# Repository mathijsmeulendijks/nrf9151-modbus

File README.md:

# nRF9151 multi-protocol industrial node

DIN-rail board (3D-printed 2-module housing, TS35): **85-264 VAC** (Mean Well IRM-10-5) -> **discrete CC supercap charger** hold-up (0.1 ohm + INA180A1 + MCP6001 + AO4407A) -> **nRF9151** cellular/GNSS with **RS-485 + RS-232 + CAN** on one RJ45.

Native **KiCad 10** project. Schematic is the source of truth for circuits; the PCB is fully placed but **unrouted** (routing is done by the board designer). The PCB stands vertical in a DIN 43880 housing (2 modules, 36 mm wide).

## Architecture

| Block | Implementation |
|-------|----------------|
| Mains in | Phoenix MKDS 1,5 2-pos 5.08 mm terminal J1 (no LCSC number yet) |
| Mains fuse | **SMD 2410 fuse** JFC2410-1100TS (1 A time-lag, 250 V, C136380) -> IRM-10-5 (C2857903) |
| Supercap charge | **Discrete CC**: 0.1 ohm sense + **INA180A1** + **MCP6001** + **AO4407A** P-FET (~0.5 A) |
| Hold-up | **3.5 F / 5.5 V** CDA CHP5R5L355R-TW (C2925904, 20x10x22 mm upright) + **dual LM66100** ideal-diode OR into VSYS |
| Surge | **SMAJ5.0A** on VSYS |
| Brownout | APX803L-29 (2.9 V UVLO -> nRESET) + VSYS ADC on P0.04 |
| 3.3 V | TLV1117-33 (peripherals + **VDD_GPIO**) |
| Modem VDD | **VSYS (~4-5 V)** through FB + bulk (not 3.3 V) |
| MCU/modem | NRF9151-LACA-R |
| RF | LTE + GNSS IPEX + **PESD5V0F1BL** RF ESD; AUX 49.9 ohm |
| SIM | Push-push nano-SIM (C7529384), **22 ohm** series, **USBLC6-2** + PESD ESD; physical SIM plus optional Onomondo SoftSIM in firmware (no eSIM lock-in) |
| RS-485 | **TI ISOW1412** isolated transceiver + iso DC-DC; **SM712** TVS |
| RS-232 | **TI MAX3232IPWR**; 2x **SMBJ15CA** TVS |
| CAN | MCP2515-I/ST TSSOP-20 (SPI, C15193) + **TI SN65HVD230** + 8 MHz crystal (C2682774); **NUP2105LT1G** on CAN H/L |
| Field I/O | Single RJ45 (KH-RJ45-56-8P8C) |
| Debug | 10-pin SWD; SWDIO 10 k up, **SWDCLK 100 k down**; no reset switch (reset via UVLO, SWD, nRESET test pad) |
| Temp | TMP117 on I2C |

## Power path

```
AC_L -> SMD fuse -> IRM-10-5 -> 5V_RAW
                         |- Rsense + P-FET CC -> supercap -+
                         '- LM66100 -----------------------+-> VSYS -+-> LDO 3V3 -> VDD_GPIO / logic
                                                           |         '-> FB -> VDD_nRF (SiP VDD)
                         supercap -> LM66100 --------------+
VSYS <- SMAJ5.0A clamp
```

**Why VDD from VSYS:** Nordic VDD is 3.0-5.5 V; RF headroom and TX efficiency are better above 3.3 V. VDD_GPIO stays at 3.3 V for ISOW / MAX3232 / CAN / SWD levels.

**Ideal diodes:** LM66100 (~95 mohm) replace a Schottky OR so hold-up loses less voltage under load.

## Supercap charge limiter (FET + op-amp)

| Piece | Role |
|-------|------|
| **0.1 ohm** 1206 sense | V_sense = I * R (50 mV @ 0.5 A) |
| **INA180A1** (20 V/V) | High-side sense -> V_fb ~ 1.0 V @ 0.5 A |
| Divider 40.2k/10k | V_ref ~ 1.0 V from 5 V |
| **MCP6001** | Error amp: V_fb > V_ref raises P-FET gate (less current) |
| **AO4407A** SOP-8 | P-FET handles linear heat; ~fully on when I < I_set for top-up |

```
I_set ~ V_ref / (G_INA * R_sense) ~ 1.0 / (20 * 0.1) = 0.5 A
```

Pour copper under AO4407A; keep sense Kelvin-ish. SMAJ5.0A clamps VSYS (not a precision CV for the 5.5 V cap, which charges to ~5V_RAW).

## Field RJ45 pinout (custom multi-bus)

| Pin | Signal |
|-----|--------|
| 1-2 | RS485_A / B (isolated; **not** board GND) |
| 3 / 6 | RS232_TX / RX |
| 4-5 | CAN_H / L |
| 7-8 | GND (RS-232 / CAN reference) |
| 9-10 | Shield -> board GND |

## MCU pin map

| Function | Pins |
|----------|------|
| RS-485 UART | P0.10 TX, P0.11 RX, P0.12 DE (/RE) |
| RS-232 UART | P0.13 TX, P0.14 RX |
| CAN SPI | P0.15 SCK, P0.16 MOSI, P0.17 MISO, P0.18 nCS, P0.19 nINT |
| I2C temp | P0.02 SDA, P0.03 SCL |
| VSYS ADC | P0.04 |

## Project files

| File | Content |
|------|---------|
| `nrf9151-modbus.kicad_pro` / `.kicad_sch` | Project and root sheet |
| `power.kicad_sch` | Mains, charger, hold-up, VSYS, 3V3, UVLO |
| `nrf9151.kicad_sch` | SiP, decoupling, RF, SIM, SWD, temp |
| `rs485.kicad_sch` | Isolated RS-485 |
| `fieldbus.kicad_sch` | Fieldbus RS-232, CAN, RJ45 |
| `nrf9151-modbus.kicad_pcb` | 4-layer, 86 x 56 mm DIN outline (body 86 x 44 + nose 41 x 12), all 144 parts on top, 49 bare test pads on the bottom, unrouted |
| `nrf9151-modbus.kicad_dru` | Custom DRC rules (JLC minimums, mains and isolation clearances) |
| `lib/jlc.kicad_sym`, `lib/jlc.pretty`, `lib/jlc.3dshapes` | Project-local LCSC part library (3D models via Git LFS) |

Board is single-sided assembly: the bottom carries only test pads for the bed-of-nails tester (incl. a 5-pad SWD row), no mains nets. See `HANDOFF.md` for decisions, SIM strategy, open items and bring-up checklist.

## Open and fabricate

1. Open `nrf9151-modbus.kicad_pro` in **KiCad 10**.
2. Run ERC and DRC (`kicad-cli pcb drc --schematic-parity`) before fab.
3. BOM/CPL: install **Bouni/kicad-jlcpcb-tools** via the Plugin and Content Manager (reads the `LCSC` field; check rotations in the JLC preview), or **bennymeg Fabrication-Toolkit >= 5.3.1**.
4. Order with JLCPCB stackup **JLC04161H-7628** (1.6 mm, 4 layer); use the JLC impedance calculator for the 50 ohm ANT/GPS microstrips.

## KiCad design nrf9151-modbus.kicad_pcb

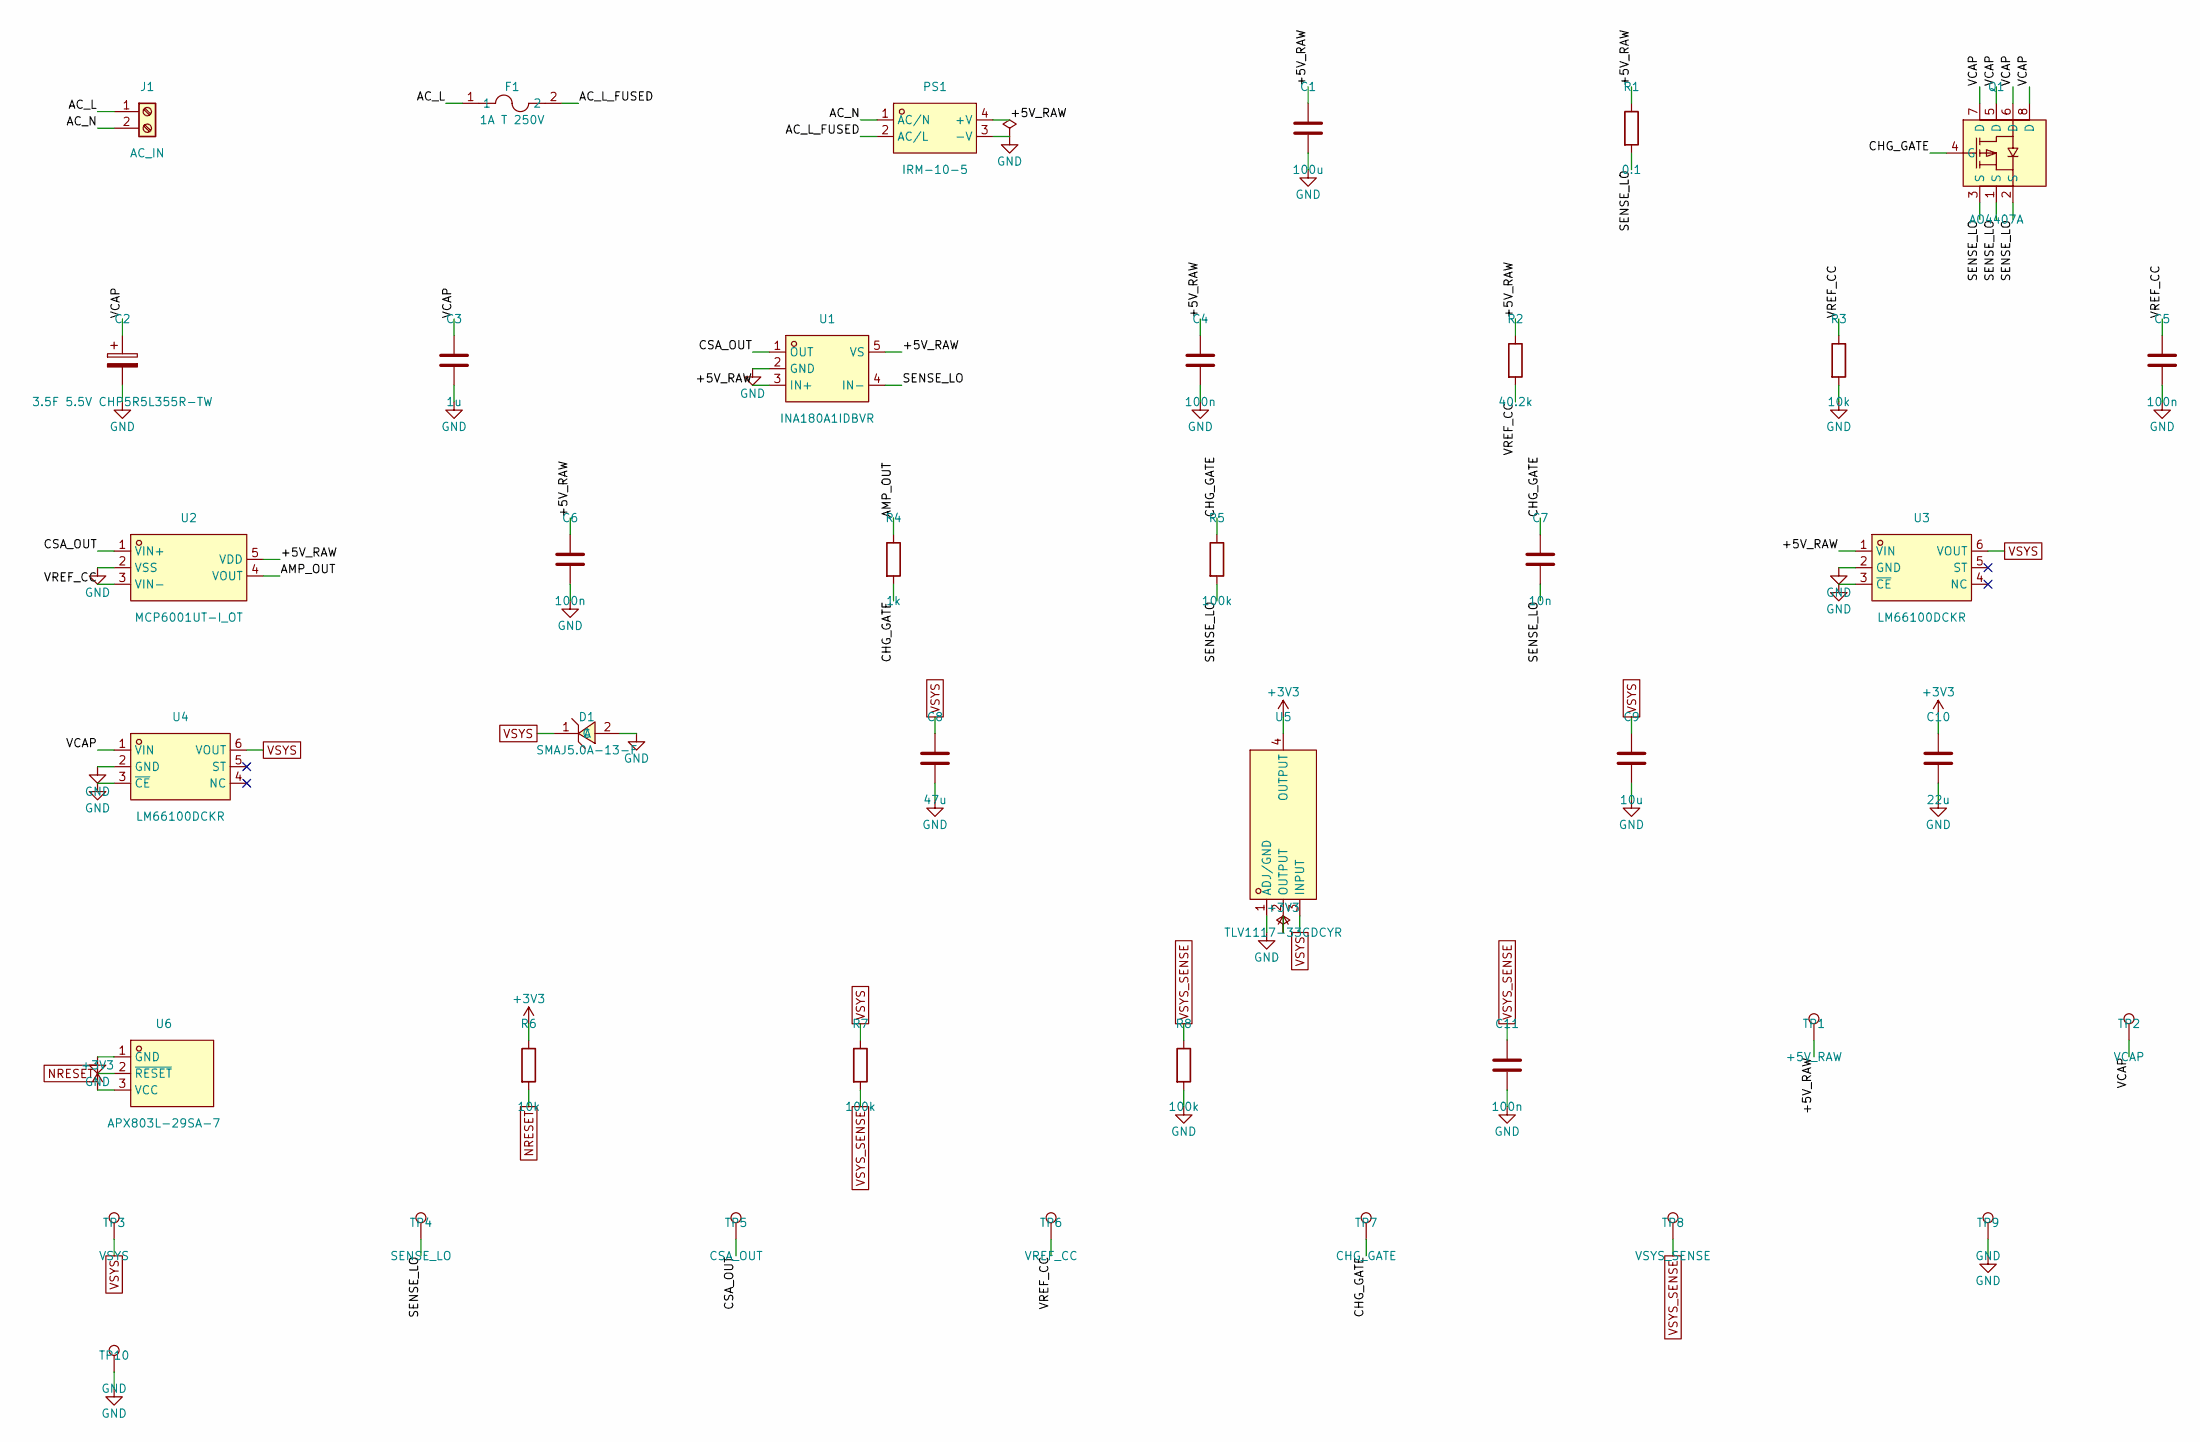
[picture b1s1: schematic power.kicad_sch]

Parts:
C1: 100u; C_1206_3216Metric; LCSC C2911415
C2: 3.5F 5.5V CHP5R5L355R-TW; CAP-TH_CDA_CHT-DA_2xD10_P15.5mm; LCSC C2925904
C3: 1u; C_0402_1005Metric; LCSC C52923
C4, C5, C6, C11: 100n; C_0402_1005Metric; LCSC C1525
C7: 10n; C_0402_1005Metric; LCSC C15195
C8: 47u; C_1206_3216Metric; LCSC C432922
C9: 10u; C_0603_1608Metric; LCSC C19702
C10: 22u; C_0603_1608Metric; LCSC C59461
D1: SMAJ5.0A-13-F; SMA_L4.3-W2.6-LS5.2-RD; LCSC C87074
F1: 1A T 250V; F2410; LCSC C136380
J1: AC_IN; TerminalBlock_Phoenix_MKDS-1,5-2-5.08_1x02_P5.08mm_Horizont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
PS1: IRM-10-5; PWRM-TH_4P-L45.7-W25.4-P8.0; LCSC C2857903
Q1: AO4407A; SOIC-8_L4.9-W3.9-P1.27-LS6.0-BL; LCSC C16072
R1: 0.1; R_1206_3216Metric; LCSC C844256
R2: 40.2k; R_0402_1005Metric; LCSC C5966383
R3, R6: 10k; R_0402_1005Metric; LCSC C25744
R4: 1k; R_0402_1005Metric; LCSC C11702
R5, R7, R8: 100k; R_0402_1005Metric; LCSC C25741
TP1: +5V_RAW; TestPoint_Pad_D1.5mm
TP2: VCAP; TestPoint_Pad_D1.5mm
TP3: VSYS; TestPoint_Pad_D1.5mm
TP4: SENSE_LO; TestPoint_Pad_D1.5mm
TP5: CSA_OUT; TestPoint_Pad_D1.5mm
TP6: VREF_CC; TestPoint_Pad_D1.5mm
TP7: CHG_GATE; TestPoint_Pad_D1.5mm
TP8: VSYS_SENSE; TestPoint_Pad_D1.5mm
TP9, TP10: GND; TestPoint_Pad_D1.5mm
U1: INA180A1IDBVR; SOT-23-5_L3.0-W1.7-P0.95-LS2.8-BR; LCSC C122228
U2: MCP6001UT-I_OT; SOT-23-5_L3.0-W1.7-P0.95-LS2.8-BR; LCSC C21403
U3, U4: LM66100DCKR; SC-70-6_L2.0-W1.3-P0.65-LS2.1-BL; LCSC C2869734
U5: TLV1117-33CDCYR; SOT-223_L6.5-W3.5-P2.30-LS7.0-BR; LCSC C91728
U6: APX803L-29SA-7; SOT-23-3_L2.9-W1.3-P1.90-LS2.4-BR; LCSC C2066862

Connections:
+3V3: C10.1, R6.1, U5.2 (OUTPUT), U5.4 (OUTPUT), U6.3 (VCC); also elsewhere on the board
/Power/+5V_RAW: C1.1, C4.1, C6.1, PS1.4 (+V), R1.1, R2.1, TP1.1, U1.3 (IN+), U1.5 (VS), U2.5 (VDD), U3.1 (VIN)
/Power/AC_L: F1.1, J1.1
/Power/AC_L_FUSED: F1.2, PS1.2 (AC/L)
/Power/AC_N: J1.2, PS1.1 (AC/N)
/Power/AMP_OUT: R4.1, U2.4 (VOUT)
/Power/CHG_GATE: C7.1, Q1.4 (G), R4.2, R5.1, TP7.1
/Power/CSA_OUT: TP5.1, U1.1 (OUT), U2.1 (VIN+)
/Power/SENSE_LO: C7.2, Q1.1 (S), Q1.2 (S), Q1.3 (S), R1.2, R5.2, TP4.1, U1.4 (IN-)
/Power/VCAP: C2.1, C3.1, Q1.5 (D), Q1.6 (D), Q1.7 (D), Q1.8 (D), TP2.1, U4.1 (VIN)
/Power/VREF_CC: C5.1, R2.2, R3.1, TP6.1, U2.3 (VIN-)
GND: C1.2, C2.2, C3.2, C4.2, C5.2, C6.2, C8.2, C9.2, C10.2, C11.2, D1.2 (A), PS1.3 (-V), R3.2, R8.2, TP9.1, TP10.1, U1.2 (GND), U2.2 (VSS), U3.2 (GND), U3.3 (~CE), U4.2 (GND), U4.3 (~CE), U5.1 (ADJ/GND), U6.1 (GND); also elsewhere on the board
NRESET: R6.2, U6.2 (~RESET); also elsewhere on the board
VSYS: C8.1, C9.1, D1.1 (C), R7.1, TP3.1, U3.6 (VOUT), U4.6 (VOUT), U5.3 (INPUT); also elsewhere on the board
VSYS_SENSE: C11.1, R7.2, R8.1, TP8.1; also elsewhere on the board

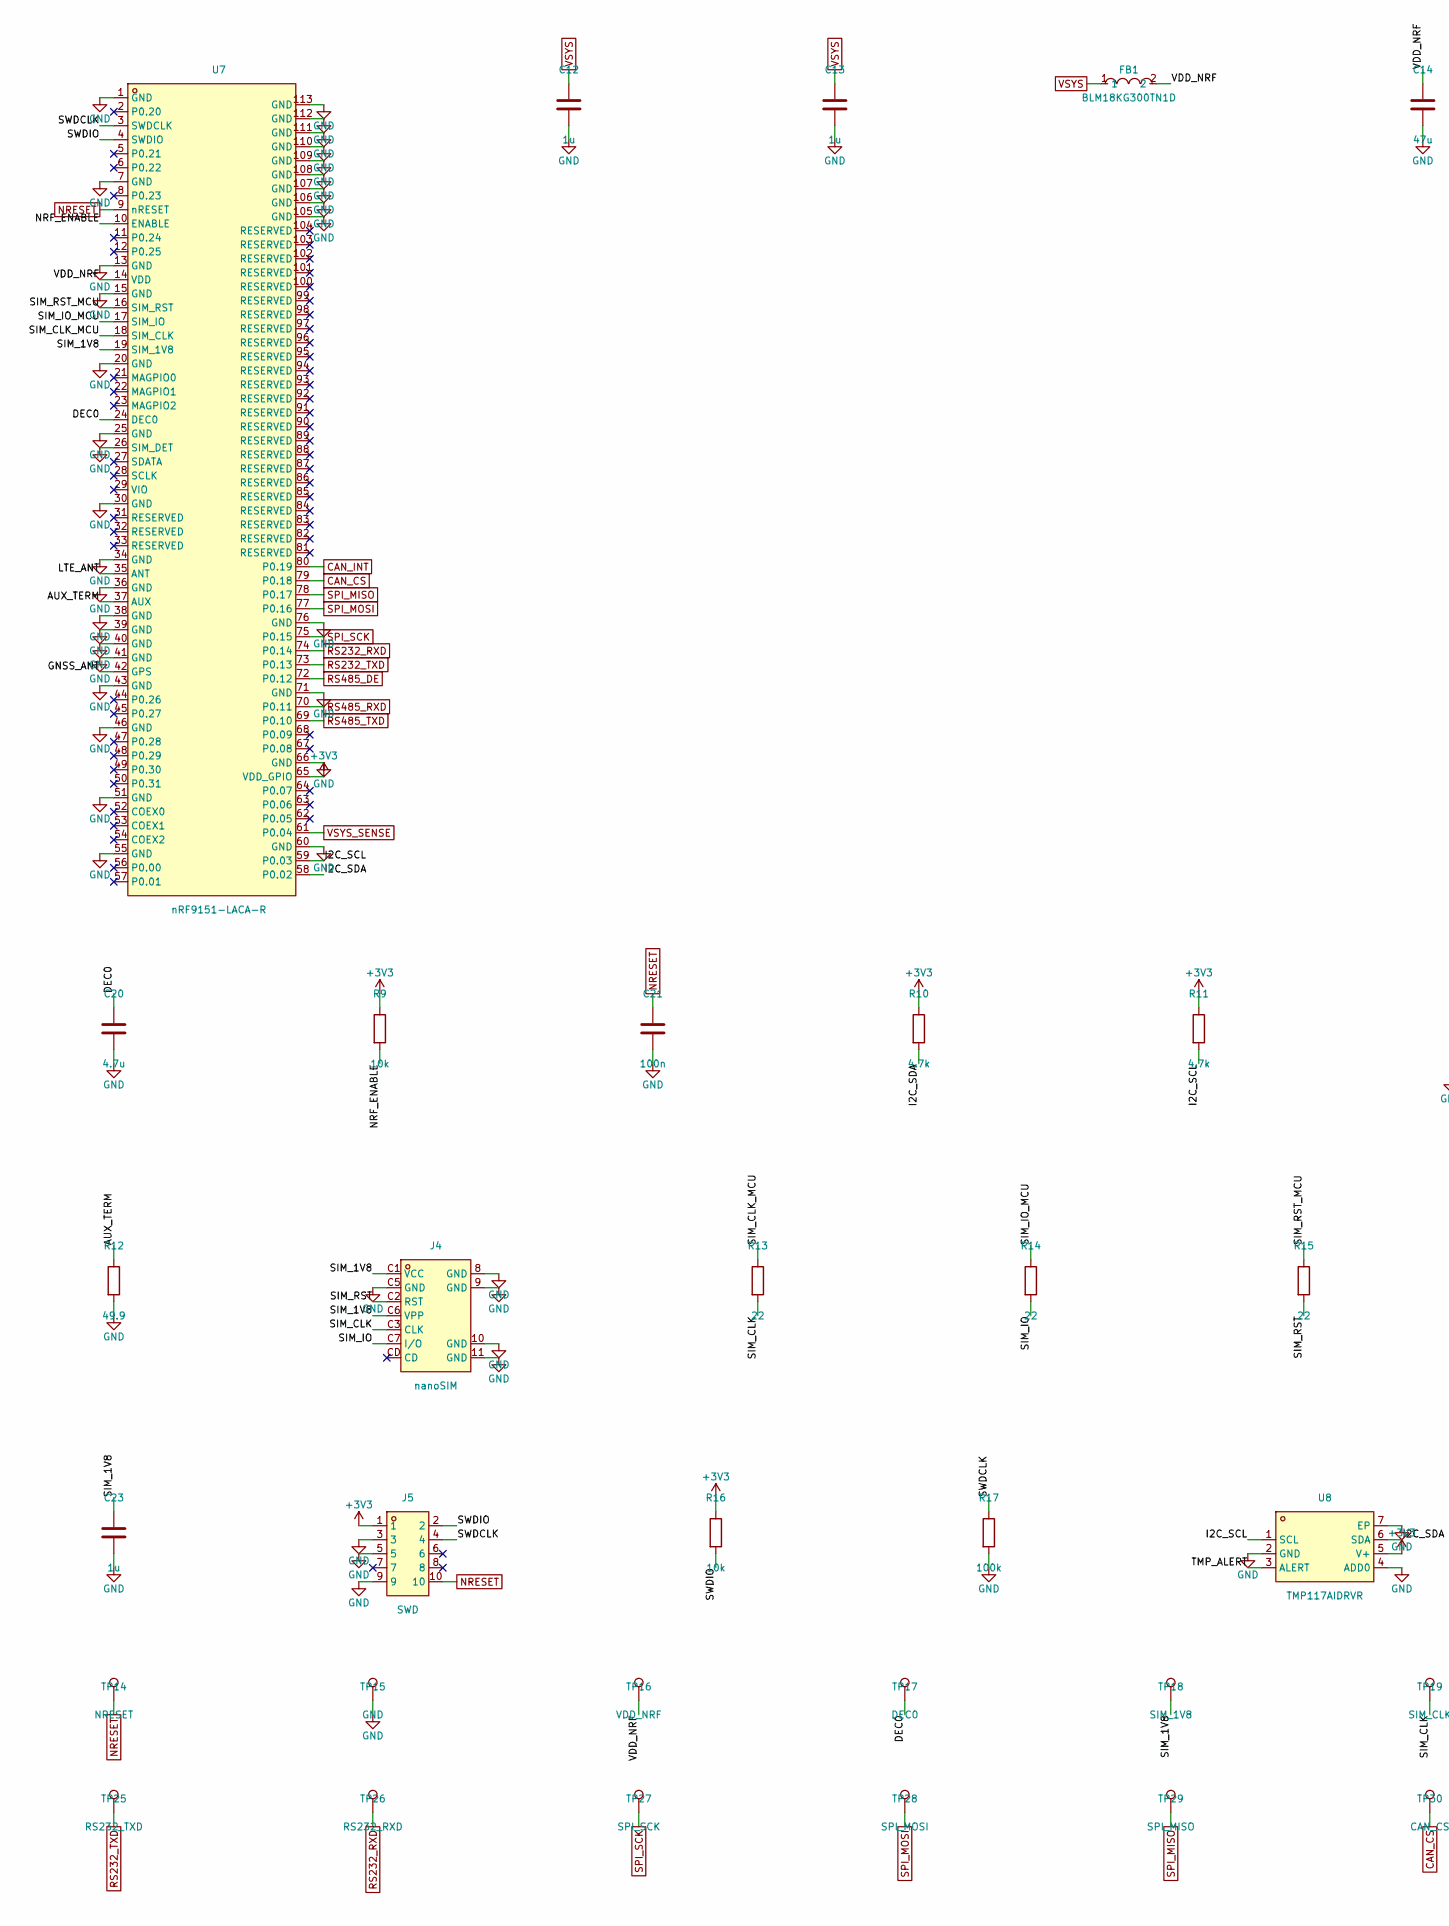
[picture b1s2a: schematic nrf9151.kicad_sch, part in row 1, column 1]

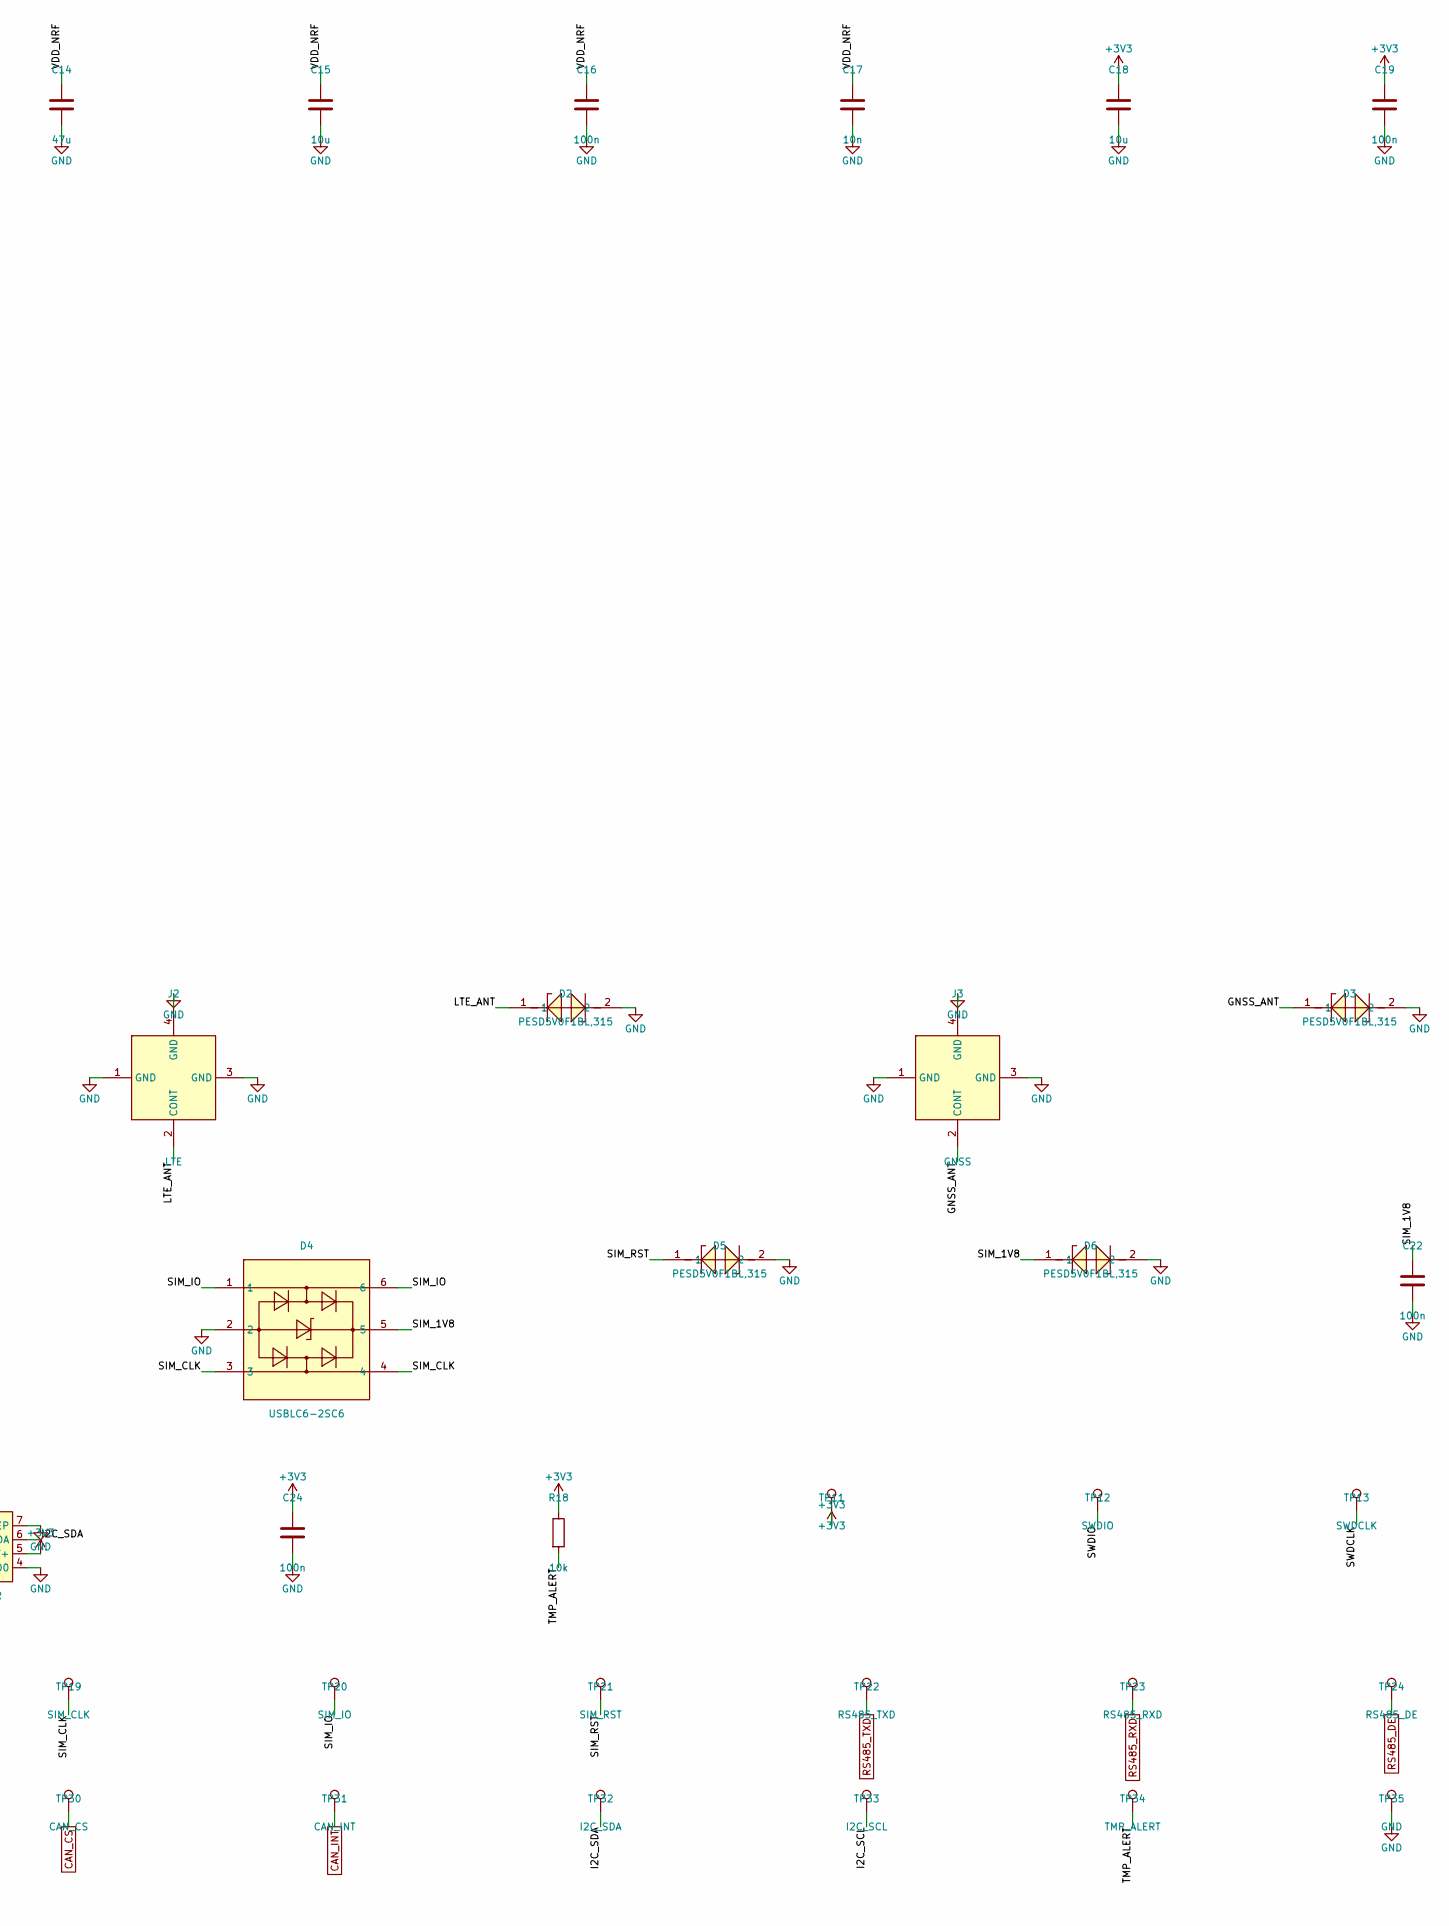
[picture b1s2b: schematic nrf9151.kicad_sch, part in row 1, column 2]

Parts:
C12, C13, C23: 1u; C_0402_1005Metric; LCSC C52923
C14: 47u; C_1206_3216Metric; LCSC C432922
C15, C18: 10u; C_0603_1608Metric; LCSC C19702
C16, C19, C21, C22, C24: 100n; C_0402_1005Metric; LCSC C1525
C17: 10n; C_0402_1005Metric; LCSC C15195
C20: 4.7u; C_0402_1005Metric; LCSC C23733
D2, D3, D5, D6: PESD5V0F1BL,315; SOD-882_L1.0-W0.6-BI; LCSC C45961
D4: USBLC6-2SC6; SOT-23-6_L2.9-W1.6-P0.95-LS2.8-BL; LCSC C7519
FB1: BLM18KG300TN1D; L0603; LCSC C88982
J2: LTE; ANT-SMD_ECT818000500; LCSC C437254
J3: GNSS; ANT-SMD_ECT818000500; LCSC C437254
J4: nanoSIM; SIM-SMD_NANO-SIM-7P-H1.37; LCSC C7529384
J5: SWD; CONN-TH_10P-P1.27_FTSH-105-01-F-D-K; LCSC C9900011230
R9, R16, R18: 10k; R_0402_1005Metric; LCSC C25744
R10, R11: 4.7k; R_0402_1005Metric; LCSC C25900
R12: 49.9; R_0402_1005Metric; LCSC C4165090
R13, R14, R15: 22; R_0402_1005Metric; LCSC C25092
R17: 100k; R_0402_1005Metric; LCSC C25741
TP11: +3V3; TestPoint_Pad_D1.5mm
TP12: SWDIO; TestPoint_Pad_D1.5mm
TP13: SWDCLK; TestPoint_Pad_D1.5mm
TP14: NRESET; TestPoint_Pad_D1.5mm
TP15, TP35: GND; TestPoint_Pad_D1.5mm
TP16: VDD_NRF; TestPoint_Pad_D1.5mm
TP17: DEC0; TestPoint_Pad_D1.5mm
TP18: SIM_1V8; TestPoint_Pad_D1.5mm
TP19: SIM_CLK; TestPoint_Pad_D1.5mm
TP20: SIM_IO; TestPoint_Pad_D1.5mm
TP21: SIM_RST; TestPoint_Pad_D1.5mm
TP22: RS485_TXD; TestPoint_Pad_D1.5mm
TP23: RS485_RXD; TestPoint_Pad_D1.5mm
TP24: RS485_DE; TestPoint_Pad_D1.5mm
TP25: RS232_TXD; TestPoint_Pad_D1.5mm
TP26: RS232_RXD; TestPoint_Pad_D1.5mm
TP27: SPI_SCK; TestPoint_Pad_D1.5mm
TP28: SPI_MOSI; TestPoint_Pad_D1.5mm
TP29: SPI_MISO; TestPoint_Pad_D1.5mm
TP30: CAN_CS; TestPoint_Pad_D1.5mm
TP31: CAN_INT; TestPoint_Pad_D1.5mm
TP32: I2C_SDA; TestPoint_Pad_D1.5mm
TP33: I2C_SCL; TestPoint_Pad_D1.5mm
TP34: TMP_ALERT; TestPoint_Pad_D1.5mm
U7: nRF9151-LACA-R; LGA-113_L12.1-W11.1_NRF9151-LACA-R7; LCSC C42236596
U8: TMP117AIDRVR; WSON-6_L2.0-W2.0-P0.65-TL-EP; LCSC C699536

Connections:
+3V3: C18.1, C19.1, C24.1, J5.1, R9.1, R10.1, R11.1, R16.1, R18.1, TP11.1, U7.65 (VDD_GPIO), U8.5 (V+); also elsewhere on the board
/nRF9151/AUX_TERM: R12.1, U7.37 (AUX)
/nRF9151/DEC0: C20.1, TP17.1, U7.24 (DEC0)
/nRF9151/GNSS_ANT: D3.1, J3.2 (CONT), U7.42 (GPS)
/nRF9151/I2C_SCL: R11.2, TP33.1, U7.59 (P0.03), U8.1 (SCL)
/nRF9151/I2C_SDA: R10.2, TP32.1, U7.58 (P0.02), U8.6 (SDA)
/nRF9151/LTE_ANT: D2.1, J2.2 (CONT), U7.35 (ANT)
/nRF9151/NRF_ENABLE: R9.2, U7.10 (ENABLE)
/nRF9151/SIM_1V8: C22.1, C23.1, D4.5, D6.1, J4.C1 (VCC), J4.C6 (VPP), TP18.1, U7.19 (SIM_1V8)
/nRF9151/SIM_CLK: D4.3, D4.4, J4.C3 (CLK), R13.2, TP19.1
/nRF9151/SIM_CLK_MCU: R13.1, U7.18 (SIM_CLK)
/nRF9151/SIM_IO: D4.1, D4.6, J4.C7 (I/O), R14.2, TP20.1
/nRF9151/SIM_IO_MCU: R14.1, U7.17 (SIM_IO)
/nRF9151/SIM_RST: D5.1, J4.C2 (RST), R15.2, TP21.1
/nRF9151/SIM_RST_MCU: R15.1, U7.16 (SIM_RST)
/nRF9151/SWDCLK: J5.4, R17.1, TP13.1, U7.3 (SWDCLK)
/nRF9151/SWDIO: J5.2, R16.2, TP12.1, U7.4 (SWDIO)
/nRF9151/TMP_ALERT: R18.2, TP34.1, U8.3 (ALERT)
/nRF9151/VDD_NRF: C14.1, C15.1, C16.1, C17.1, FB1.2, TP16.1, U7.14 (VDD)
CAN_CS: TP30.1, U7.79 (P0.18); also elsewhere on the board
CAN_INT: TP31.1, U7.80 (P0.19); also elsewhere on the board
GND: C12.2, C13.2, C14.2, C15.2, C16.2, C17.2, C18.2, C19.2, C20.2, C21.2, C22.2, C23.2, C24.2, D2.2, D3.2, D4.2, D5.2, D6.2, J2.1 (GND), J2.3 (GND), J2.4 (GND), J3.1 (GND), J3.3 (GND), J3.4 (GND), J4.8 (GND), J4.9 (GND), J4.10 (GND), J4.11 (GND), J4.C5 (GND), J5.3, J5.5, J5.9, R12.2, R17.2, TP15.1, TP35.1, U7.1 (GND), U7.7 (GND), U7.13 (GND), U7.15 (GND), U7.20 (GND), U7.25 (GND), U7.26 (SIM_DET), U7.30 (GND), U7.34 (GND), U7.36 (GND), U7.38 (GND), U7.39 (GND), U7.40 (GND), U7.41 (GND), U7.43 (GND), U7.46 (GND), U7.51 (GND), U7.55 (GND), U7.60 (GND), U7.66 (GND), U7.71 (GND), U7.76 (GND), U7.105 (GND), U7.106 (GND), U7.107 (GND), U7.108 (GND), U7.109 (GND), U7.110 (GND), U7.111 (GND), U7.112 (GND), U7.113 (GND), U8.2 (GND), U8.4 (ADD0), U8.7 (EP); also elsewhere on the board
NRESET: C21.1, J5.10, TP14.1, U7.9 (nRESET); also elsewhere on the board
RS232_RXD: TP26.1, U7.74 (P0.14); also elsewhere on the board
RS232_TXD: TP25.1, U7.73 (P0.13); also elsewhere on the board
RS485_DE: TP24.1, U7.72 (P0.12); also elsewhere on the board
RS485_RXD: TP23.1, U7.70 (P0.11); also elsewhere on the board
RS485_TXD: TP22.1, U7.69 (P0.10); also elsewhere on the board
SPI_MISO: TP29.1, U7.78 (P0.17); also elsewhere on the board
SPI_MOSI: TP28.1, U7.77 (P0.16); also elsewhere on the board
SPI_SCK: TP27.1, U7.75 (P0.15); also elsewhere on the board
VSYS: C12.1, C13.1, FB1.1; also elsewhere on the board
VSYS_SENSE: U7.61 (P0.04); also elsewhere on the board

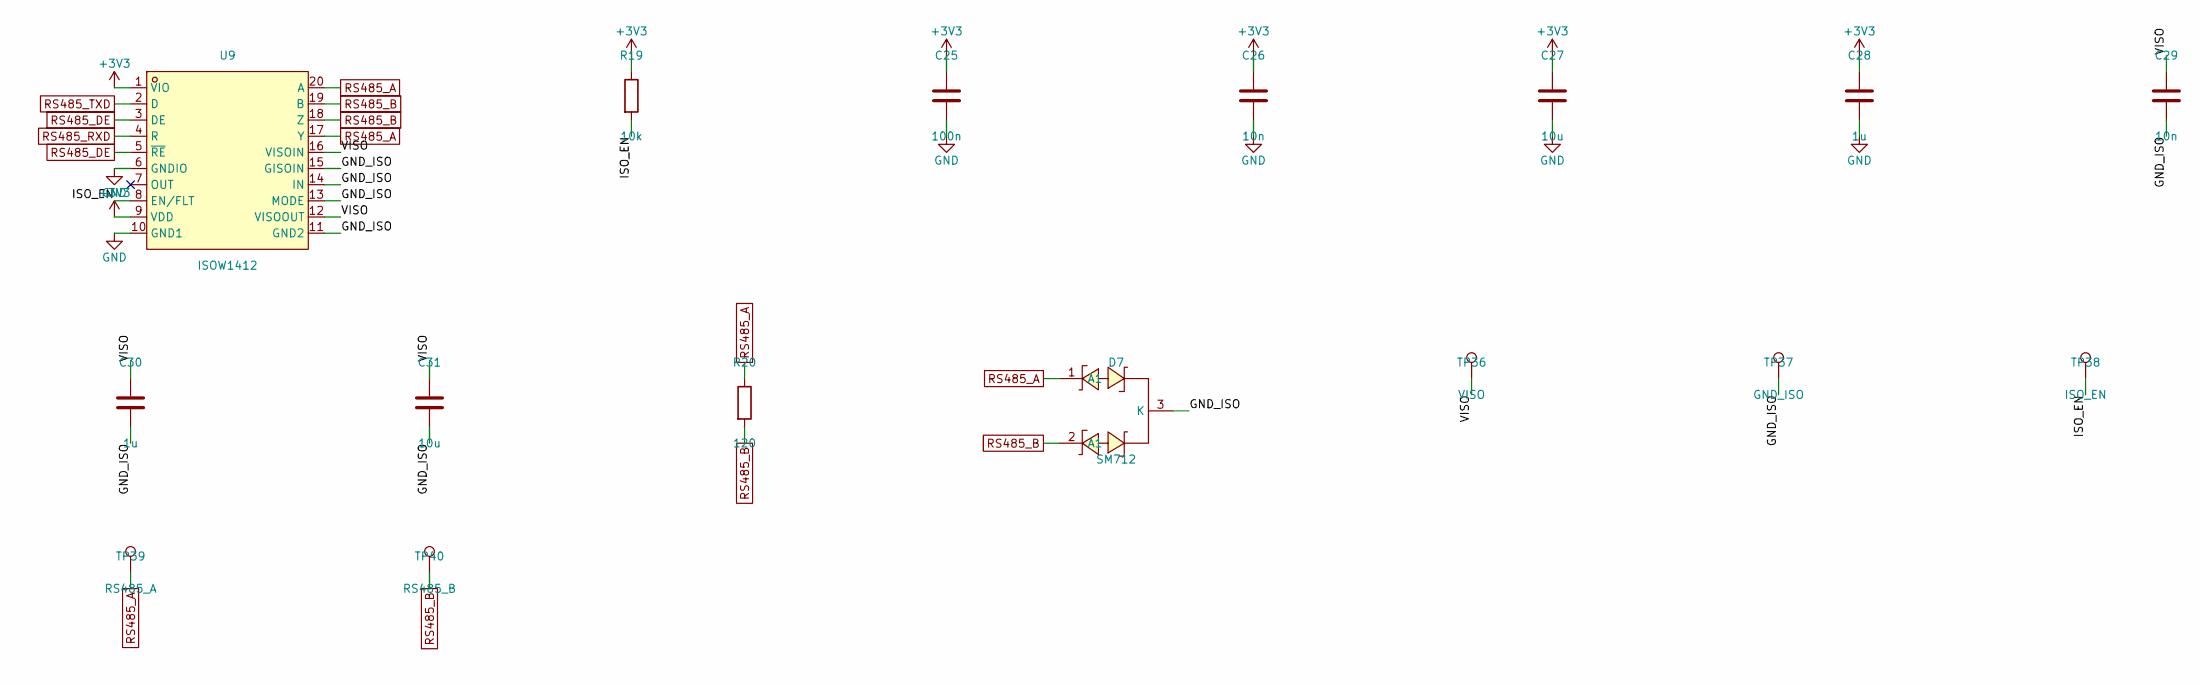
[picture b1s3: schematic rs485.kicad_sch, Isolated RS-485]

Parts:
C25: 100n; C_0402_1005Metric; LCSC C1525
C26, C29: 10n; C_0402_1005Metric; LCSC C15195
C27, C31: 10u; C_0603_1608Metric; LCSC C19702
C28, C30: 1u; C_0402_1005Metric; LCSC C52923
D7: SM712; SOT-23-3_L3.0-W1.7-P0.95-LS2.9-BR; LCSC C12067
R19: 10k; R_0402_1005Metric; LCSC C25744
R20: 120; R_0402_1005Metric; LCSC C25079
TP36: VISO; TestPoint_Pad_D1.5mm
TP37: GND_ISO; TestPoint_Pad_D1.5mm
TP38: ISO_EN; TestPoint_Pad_D1.5mm
TP39: RS485_A; TestPoint_Pad_D1.5mm
TP40: RS485_B; TestPoint_Pad_D1.5mm
U9: ISOW1412; SOIC-20_L12.8-W7.5-P1.27-LS10.3-TL; LCSC C5216548

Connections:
+3V3: C25.1, C26.1, C27.1, C28.1, R19.1, U9.1 (VIO), U9.9 (VDD); also elsewhere on the board
/Isolated RS-485/GND_ISO: C29.2, C30.2, C31.2, D7.3 (K), TP37.1, U9.11 (GND2), U9.13 (MODE), U9.14 (IN), U9.15 (GISOIN)
/Isolated RS-485/ISO_EN: R19.2, TP38.1, U9.8 (EN/FLT)
/Isolated RS-485/VISO: C29.1, C30.1, C31.1, TP36.1, U9.12 (VISOOUT), U9.16 (VISOIN)
GND: C25.2, C26.2, C27.2, C28.2, U9.6 (GNDIO), U9.10 (GND1); also elsewhere on the board
RS485_A: D7.1 (A1), R20.1, TP39.1, U9.17 (Y), U9.20 (A); also elsewhere on the board
RS485_B: D7.2 (A1), R20.2, TP40.1, U9.18 (Z), U9.19 (B); also elsewhere on the board
RS485_DE: U9.3 (DE), U9.5 (~RE); also elsewhere on the board
RS485_RXD: U9.4 (R); also elsewhere on the board
RS485_TXD: U9.2 (D); also elsewhere on the board

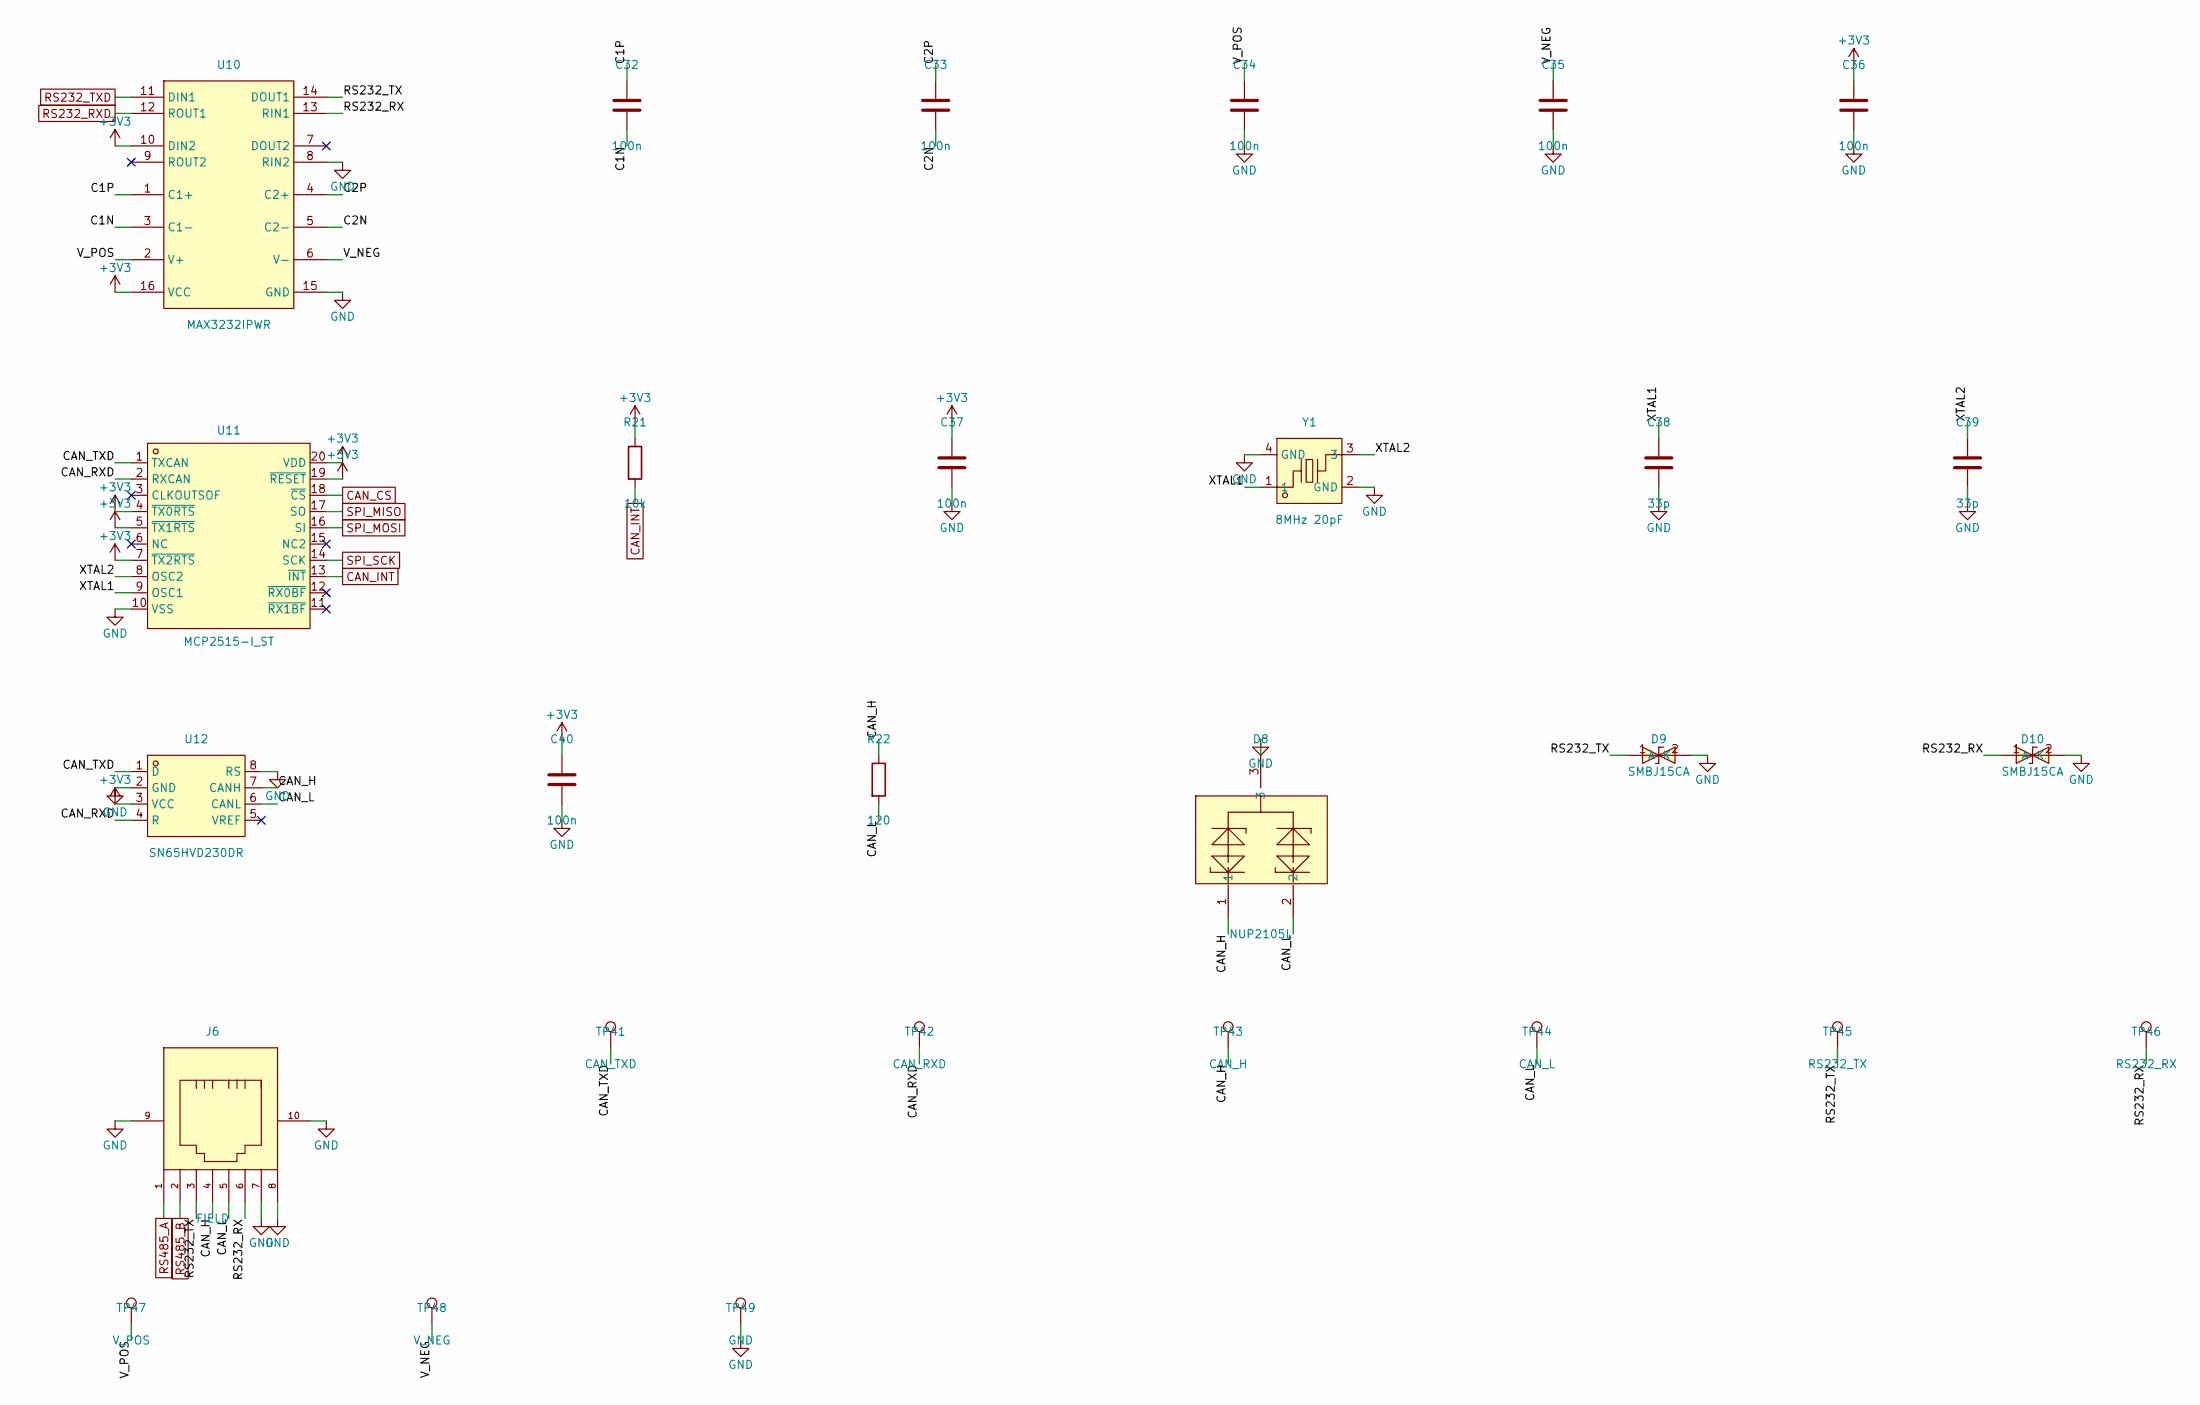
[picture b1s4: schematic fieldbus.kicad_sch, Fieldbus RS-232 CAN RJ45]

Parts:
C32, C33, C34, C35, C36, C37, C40: 100n; C_0402_1005Metric; LCSC C1525
C38, C39: 33p; C_0402_1005Metric; LCSC C1562
D8: NUP2105L; SOT-23-3_L2.9-W1.3-P1.90-LS2.4-BL-2; LCSC C14486
D9, D10: SMBJ15CA; SMB_L4.6-W3.6-LS5.3-BI; LCSC C78809
J6: FIELD; RJ45-TH_KH-RJ45-56-8P8C; LCSC C2683359
R21: 10k; R_0402_1005Metric; LCSC C25744
R22: 120; R_0402_1005Metric; LCSC C25079
TP41: CAN_TXD; TestPoint_Pad_D1.5mm
TP42: CAN_RXD; TestPoint_Pad_D1.5mm
TP43: CAN_H; TestPoint_Pad_D1.5mm
TP44: CAN_L; TestPoint_Pad_D1.5mm
TP45: RS232_TX; TestPoint_Pad_D1.5mm
TP46: RS232_RX; TestPoint_Pad_D1.5mm
TP47: V_POS; TestPoint_Pad_D1.5mm
TP48: V_NEG; TestPoint_Pad_D1.5mm
TP49: GND; TestPoint_Pad_D1.5mm
U10: MAX3232IPWR; TSSOP-16_L5.0-W4.4-P0.65-LS6.4-BL; LCSC C113205
U11: MCP2515-I_ST; TSSOP-20_L6.5-W4.4-P0.65-LS6.4-BL; LCSC C15193
U12: SN65HVD230DR; SOIC-8_L4.9-W3.9-P1.27-LS6.0-BL; LCSC C12084
Y1: 8MHz 20pF; CRYSTAL-SMD_4P-L3.2-W2.5-BL; LCSC C2682774

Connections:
+3V3: C36.1, C37.1, C40.1, R21.1, U10.10 (DIN2), U10.16 (VCC), U11.4 (~TX0RTS), U11.5 (~TX1RTS), U11.7 (~TX2RTS), U11.19 (~RESET), U11.20 (VDD), U12.3 (VCC); also elsewhere on the board
/Fieldbus RS-232 CAN RJ45/C1N: C32.2, U10.3 (C1-)
/Fieldbus RS-232 CAN RJ45/C1P: C32.1, U10.1 (C1+)
/Fieldbus RS-232 CAN RJ45/C2N: C33.2, U10.5 (C2-)
/Fieldbus RS-232 CAN RJ45/C2P: C33.1, U10.4 (C2+)
/Fieldbus RS-232 CAN RJ45/CAN_H: D8.1, J6.4, R22.1, TP43.1, U12.7 (CANH)
/Fieldbus RS-232 CAN RJ45/CAN_L: D8.2, J6.5, R22.2, TP44.1, U12.6 (CANL)
/Fieldbus RS-232 CAN RJ45/CAN_RXD: TP42.1, U11.2 (RXCAN), U12.4 (R)
/Fieldbus RS-232 CAN RJ45/CAN_TXD: TP41.1, U11.1 (TXCAN), U12.1 (D)
/Fieldbus RS-232 CAN RJ45/RS232_RX: D10.1 (K), J6.6, TP46.1, U10.13 (RIN1)
/Fieldbus RS-232 CAN RJ45/RS232_TX: D9.1 (K), J6.3, TP45.1, U10.14 (DOUT1)
/Fieldbus RS-232 CAN RJ45/V_NEG: C35.1, TP48.1, U10.6 (V-)
/Fieldbus RS-232 CAN RJ45/V_POS: C34.1, TP47.1, U10.2 (V+)
/Fieldbus RS-232 CAN RJ45/XTAL1: C38.1, U11.9 (OSC1), Y1.1
/Fieldbus RS-232 CAN RJ45/XTAL2: C39.1, U11.8 (OSC2), Y1.3
CAN_CS: U11.18 (~CS); also elsewhere on the board
CAN_INT: R21.2, U11.13 (~INT); also elsewhere on the board
GND: C34.2, C35.2, C36.2, C37.2, C38.2, C39.2, C40.2, D8.3, D9.2 (A), D10.2 (A), J6.7, J6.8, J6.9, J6.10, TP49.1, U10.8 (RIN2), U10.15 (GND), U11.10 (VSS), U12.2 (GND), U12.8 (RS), Y1.2 (GND), Y1.4 (GND); also elsewhere on the board
RS232_RXD: U10.12 (ROUT1); also elsewhere on the board
RS232_TXD: U10.11 (DIN1); also elsewhere on the board
RS485_A: J6.1; also elsewhere on the board
RS485_B: J6.2; also elsewhere on the board
SPI_MISO: U11.17 (SO); also elsewhere on the board
SPI_MOSI: U11.16 (SI); also elsewhere on the board
SPI_SCK: U11.14 (SCK); also elsewhere on the board

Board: 4 copper layers, 144 parts (49 on the bottom side), 62 nets, no tracks yet.
